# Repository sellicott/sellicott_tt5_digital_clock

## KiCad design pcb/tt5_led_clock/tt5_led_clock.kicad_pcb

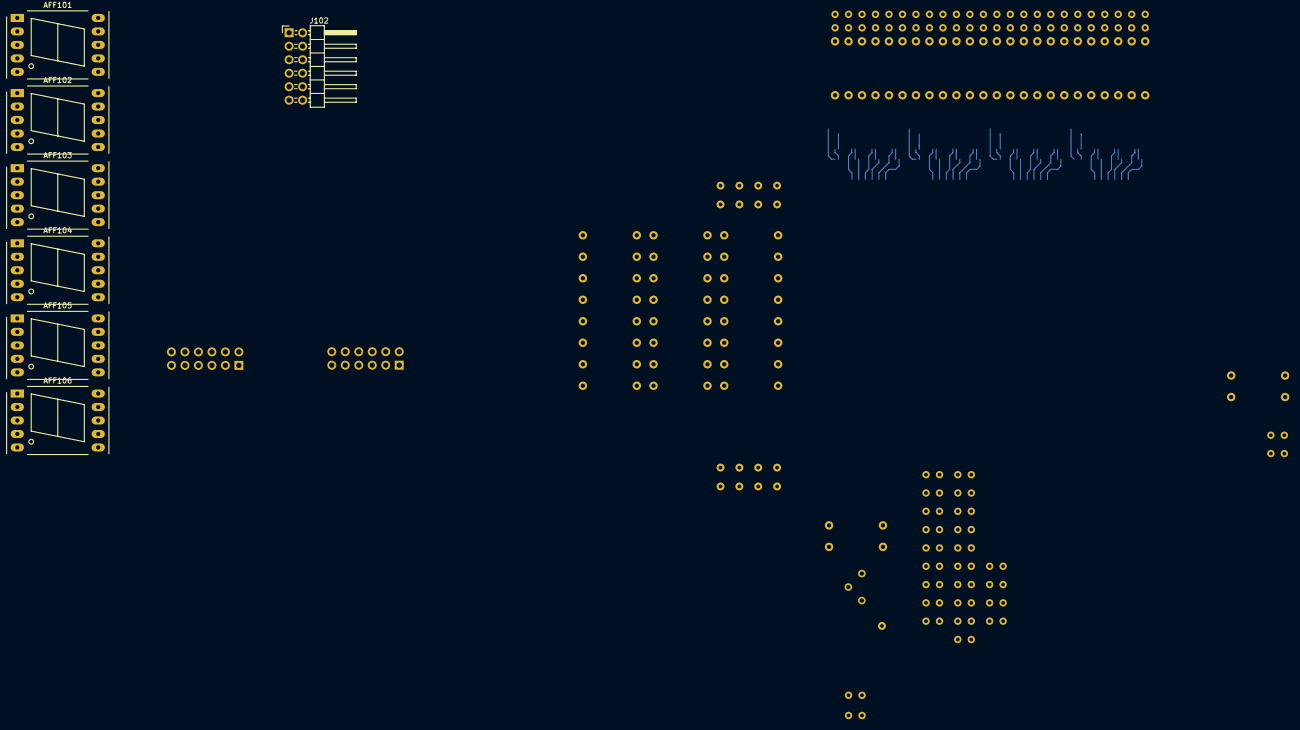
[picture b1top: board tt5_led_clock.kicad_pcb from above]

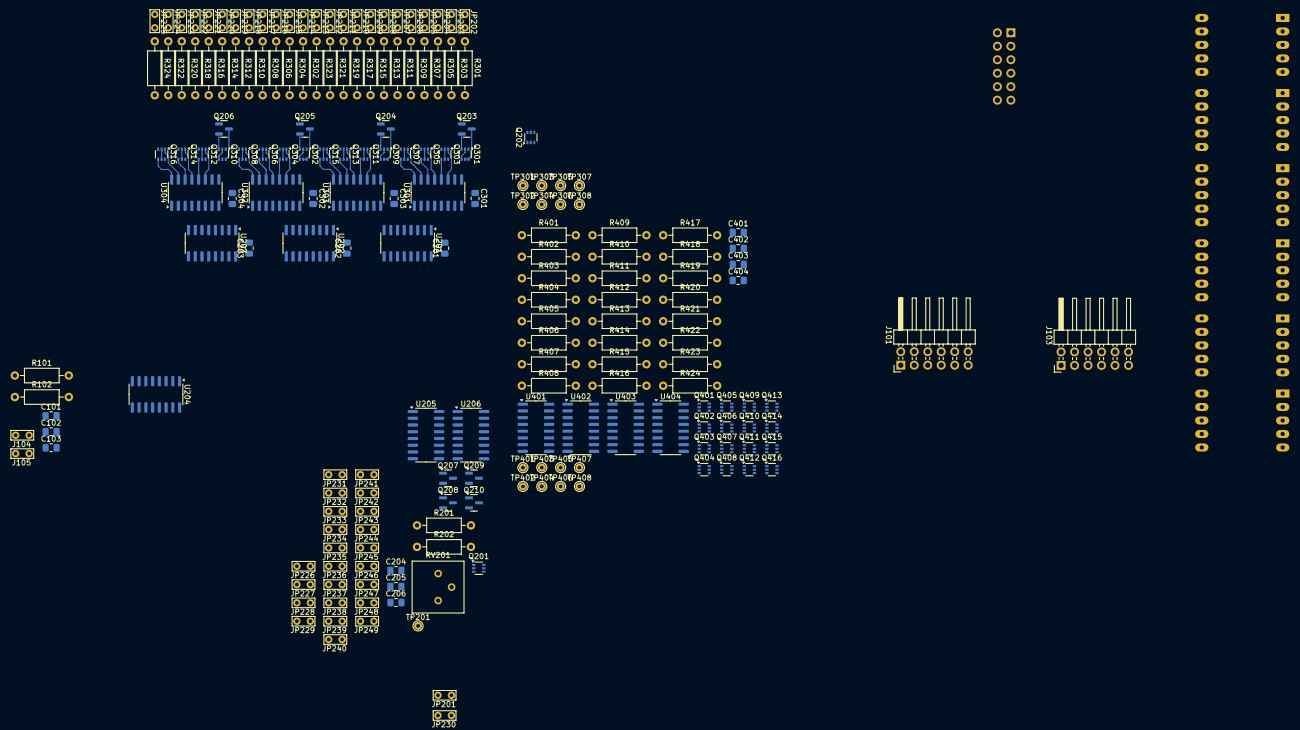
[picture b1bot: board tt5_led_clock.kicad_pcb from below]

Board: 2 copper layers, 203 parts (196 on the bottom side), 188 nets.

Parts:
AFF101, AFF102, AFF103, AFF104, AFF105, AFF106: LTS-6980HR; 7SegmentLED_LTS6760_LTS6780
C101: 10u; C_0805_2012Metric_Pad1.18x1.45mm_HandSolder
C102, C301, C302, C303, C304, C401, C402, C403, C404: 100n; C_0805_2012Metric_Pad1.18x1.45mm_HandSolder
C103: 22u; C_0805_2012Metric_Pad1.18x1.45mm_HandSolder
C201, C202, C203, C204, C205, C206: 1n; C_0805_2012Metric_Pad1.18x1.45mm_HandSolder
J101: Input; PinHeader_2x06_P2.54mm_Horizontal
J102: Bidir; PinHeader_2x06_P2.54mm_Horizontal
J103: Output; PinHeader_2x06_P2.54mm_Horizontal
J104: USB_C_Receptacle_USB2.0_16P; TestPoint_Bridge_Pitch2.54mm_Drill0.7mm
J105: Conn_01x08; TestPoint_Bridge_Pitch2.54mm_Drill0.7mm
JP201, JP202, JP203, JP204, JP205, JP206, JP207, JP208, JP209, JP210, JP211, JP212, JP213, JP214, JP215, JP216, JP217, JP218, JP219, JP220, JP221, JP222, JP223, JP224, JP225, JP226, JP227, JP228, JP229, JP230, JP231, JP232, JP233, JP234, JP235, JP236, JP237, JP238, JP239, JP240, JP241, JP242, JP243, JP244, JP245, JP246, JP247, JP248, JP249: Jumper_2_Bridged; TestPoint_Bridge_Pitch2.54mm_Drill0.7mm
Q201, Q301, Q302, Q303, Q304, Q305, Q306, Q307, Q308, Q309, Q310, Q311, Q312, Q313, Q314, Q315, Q316, Q401, Q402, Q403, Q404, Q405, Q406, Q407, Q408, Q409, Q410, Q411, Q412, Q413, Q414, Q415, Q416: MMDT3904; SOT-363_SC-70-6
Q202: MMDT3906; SOT-363_SC-70-6
Q203, Q204, Q205, Q206, Q207, Q208, Q209, Q210: MMBT3906; SOT-23
R101, R102: 5k1; R_Axial_DIN0207_L6.3mm_D2.5mm_P10.16mm_Horizontal
R201: 10K; R_Axial_DIN0207_L6.3mm_D2.5mm_P10.16mm_Horizontal
R202: 330R; R_Axial_DIN0207_L6.3mm_D2.5mm_P10.16mm_Horizontal
R301, R302, R303, R304, R305, R306, R307, R309, R310, R311, R312, R313, R314, R316, R317, R318, R319, R320, R321, R322, R323, R401, R402, R403, R404, R405, R406, R407, R409, R410, R411, R412, R413, R414, R416, R417, R418, R419, R420, R421, R422, R423: 1k4; R_Axial_DIN0207_L6.3mm_D2.5mm_P10.16mm_Horizontal
R308, R315, R324, R408, R415, R424: 2k8; R_Axial_DIN0207_L6.3mm_D2.5mm_P10.16mm_Horizontal
RV201: 1k; Potentiometer_Bourns_3386P_Vertical
TP201: segment_cm; TestPoint_THTPad_D1.5mm_Drill0.7mm
TP301, TP401: s1_iref; TestPoint_THTPad_D1.5mm_Drill0.7mm
TP302, TP402: s3_iref; TestPoint_THTPad_D1.5mm_Drill0.7mm
TP303, TP403: s1_mirror; TestPoint_THTPad_D1.5mm_Drill0.7mm
TP304, TP404: s3_mirror; TestPoint_THTPad_D1.5mm_Drill0.7mm
TP305, TP405: s2_iref; TestPoint_THTPad_D1.5mm_Drill0.7mm
TP306, TP406: s4_iref; TestPoint_THTPad_D1.5mm_Drill0.7mm
TP307, TP407: s2_mirror; TestPoint_THTPad_D1.5mm_Drill0.7mm
TP308, TP408: s4_mirror; TestPoint_THTPad_D1.5mm_Drill0.7mm
U201, U202, U203, U204, U205, U206: 74HC595; SOIC-16_3.9x9.9mm_P1.27mm
U301, U302, U303, U304, U401, U402, U403, U404: ULN2003; SOIC-16_3.9x9.9mm_P1.27mm

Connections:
+3.3V: C102.1, C103.1
/LED_CC_drivers/LED_Drivers_High/e1_s1a: Q303.1 (E1), R301.2, U301.11 (O6)
/LED_CC_drivers/LED_Drivers_High/e1_s1b: Q303.4 (E2), R303.2, U301.12 (O5)
/LED_CC_drivers/LED_Drivers_High/e1_s1c: Q305.1 (E1), R305.2, U301.13 (O4)
/LED_CC_drivers/LED_Drivers_High/e1_s1d: Q305.4 (E2), R307.2, U301.14 (O3)
/LED_CC_drivers/LED_Drivers_High/e1_s1e: Q307.1 (E1), R309.2, U301.15 (O2)
/LED_CC_drivers/LED_Drivers_High/e1_s1f: Q307.4 (E2), R311.2, U301.16 (O1)
/LED_CC_drivers/LED_Drivers_High/e2_s1dp: Q311.4 (E2), R315.2, U303.12 (O5)
/LED_CC_drivers/LED_Drivers_High/e2_s1g: Q311.1 (E1), R313.2, U303.11 (O6)
/LED_CC_drivers/LED_Drivers_High/e2_s2a: Q313.1 (E1), R317.2, U303.13 (O4)
/LED_CC_drivers/LED_Drivers_High/e2_s2b: Q313.4 (E2), R319.2, U303.14 (O3)
/LED_CC_drivers/LED_Drivers_High/e2_s2c: Q315.1 (E1), R321.2, U303.15 (O2)
/LED_CC_drivers/LED_Drivers_High/e2_s2d: Q315.4 (E2), R323.2, U303.16 (O1)
/LED_CC_drivers/LED_Drivers_High/e3_s2dp: Q306.4 (E2), R308.2, U302.14 (O3)
/LED_CC_drivers/LED_Drivers_High/e3_s2e: Q304.1 (E1), R302.2, U302.11 (O6)
/LED_CC_drivers/LED_Drivers_High/e3_s2f: Q304.4 (E2), R304.2, U302.12 (O5)
/LED_CC_drivers/LED_Drivers_High/e3_s2g: Q306.1 (E1), R306.2, U302.13 (O4)
/LED_CC_drivers/LED_Drivers_High/e3_s3a: Q308.1 (E1), R310.2, U302.15 (O2)
/LED_CC_drivers/LED_Drivers_High/e3_s3b: Q308.4 (E2), R312.2, U302.16 (O1)
/LED_CC_drivers/LED_Drivers_High/e4_s3c: Q312.1 (E1), R314.2, U304.11 (O6)
/LED_CC_drivers/LED_Drivers_High/e4_s3d: Q312.4 (E2), R316.2, U304.12 (O5)
/LED_CC_drivers/LED_Drivers_High/e4_s3dp: Q316.4 (E2), R324.2, U304.16 (O1)
/LED_CC_drivers/LED_Drivers_High/e4_s3e: Q314.1 (E1), R318.2, U304.13 (O4)
/LED_CC_drivers/LED_Drivers_High/e4_s3f: Q314.4 (E2), R320.2, U304.14 (O3)
/LED_CC_drivers/LED_Drivers_High/e4_s3g: Q316.1 (E1), R322.2, U304.15 (O2)
/LED_CC_drivers/LED_Drivers_High/iref1: Q203.3 (C), Q301.5 (B2), Q301.6 (C1), TP301.1
/LED_CC_drivers/LED_Drivers_High/iref2: Q204.3 (C), Q309.5 (B2), Q309.6 (C1), TP305.1
/LED_CC_drivers/LED_Drivers_High/iref3: Q205.3 (C), Q302.5 (B2), Q302.6 (C1), TP302.1
/LED_CC_drivers/LED_Drivers_High/iref4: Q206.3 (C), Q310.5 (B2), Q310.6 (C1), TP306.1
/LED_CC_drivers/LED_Drivers_High/o1_s1a: JP202.1 (A), Q303.6 (C1), R301.1
/LED_CC_drivers/LED_Drivers_High/o1_s1b: JP203.1 (A), Q303.3 (C2), R303.1
/LED_CC_drivers/LED_Drivers_High/o1_s1c: JP204.1 (A), Q305.6 (C1), R305.1
/LED_CC_drivers/LED_Drivers_High/o1_s1d: JP205.1 (A), Q305.3 (C2), R307.1
/LED_CC_drivers/LED_Drivers_High/o1_s1e: JP206.1 (A), Q307.6 (C1), R309.1
/LED_CC_drivers/LED_Drivers_High/o1_s1f: JP207.1 (A), Q307.3 (C2), R311.1
/LED_CC_drivers/LED_Drivers_High/o2_s1dp: JP209.1 (A), Q311.3 (C2), R315.1
/LED_CC_drivers/LED_Drivers_High/o2_s1g: JP208.1 (A), Q311.6 (C1), R313.1
/LED_CC_drivers/LED_Drivers_High/o2_s2a: JP210.1 (A), Q313.6 (C1), R317.1
/LED_CC_drivers/LED_Drivers_High/o2_s2b: JP211.1 (A), Q313.3 (C2), R319.1
/LED_CC_drivers/LED_Drivers_High/o2_s2c: JP212.1 (A), Q315.6 (C1), R321.1
/LED_CC_drivers/LED_Drivers_High/o2_s2d: JP213.1 (A), Q315.3 (C2), R323.1
/LED_CC_drivers/LED_Drivers_High/o3_s2dp: JP217.1 (A), Q306.3 (C2), R308.1
/LED_CC_drivers/LED_Drivers_High/o3_s2e: JP214.1 (A), Q304.6 (C1), R302.1
/LED_CC_drivers/LED_Drivers_High/o3_s2f: JP215.1 (A), Q304.3 (C2), R304.1
/LED_CC_drivers/LED_Drivers_High/o3_s2g: JP216.1 (A), Q306.6 (C1), R306.1
/LED_CC_drivers/LED_Drivers_High/o3_s3a: JP218.1 (A), Q308.6 (C1), R310.1
/LED_CC_drivers/LED_Drivers_High/o3_s3b: JP219.1 (A), Q308.3 (C2), R312.1
/LED_CC_drivers/LED_Drivers_High/o4_s3c: JP220.1 (A), Q312.6 (C1), R314.1
/LED_CC_drivers/LED_Drivers_High/o4_s3d: JP221.1 (A), Q312.3 (C2), R316.1
/LED_CC_drivers/LED_Drivers_High/o4_s3dp: JP225.1 (A), Q316.3 (C2), R324.1
/LED_CC_drivers/LED_Drivers_High/o4_s3e: JP222.1 (A), Q314.6 (C1), R318.1
/LED_CC_drivers/LED_Drivers_High/o4_s3f: JP223.1 (A), Q314.3 (C2), R320.1
/LED_CC_drivers/LED_Drivers_High/o4_s3g: JP224.1 (A), Q316.6 (C1), R322.1
/LED_CC_drivers/LED_Drivers_Low/e1_s1a: Q403.1 (E1), R401.2, U401.11 (O6)
/LED_CC_drivers/LED_Drivers_Low/e1_s1b: Q403.4 (E2), R403.2, U401.12 (O5)
/LED_CC_drivers/LED_Drivers_Low/e1_s1c: Q405.1 (E1), R405.2, U401.13 (O4)
/LED_CC_drivers/LED_Drivers_Low/e1_s1d: Q405.4 (E2), R407.2, U401.14 (O3)
/LED_CC_drivers/LED_Drivers_Low/e1_s1e: Q407.1 (E1), R409.2, U401.15 (O2)
/LED_CC_drivers/LED_Drivers_Low/e1_s1f: Q407.4 (E2), R411.2, U401.16 (O1)
/LED_CC_drivers/LED_Drivers_Low/e2_s1dp: Q411.4 (E2), R415.2, U403.12 (O5)
/LED_CC_drivers/LED_Drivers_Low/e2_s1g: Q411.1 (E1), R413.2, U403.11 (O6)
/LED_CC_drivers/LED_Drivers_Low/e2_s2a: Q413.1 (E1), R417.2, U403.13 (O4)
/LED_CC_drivers/LED_Drivers_Low/e2_s2b: Q413.4 (E2), R419.2, U403.14 (O3)
/LED_CC_drivers/LED_Drivers_Low/e2_s2c: Q415.1 (E1), R421.2, U403.15 (O2)
/LED_CC_drivers/LED_Drivers_Low/e2_s2d: Q415.4 (E2), R423.2, U403.16 (O1)
/LED_CC_drivers/LED_Drivers_Low/e3_s2dp: Q406.4 (E2), R408.2, U402.14 (O3)
/LED_CC_drivers/LED_Drivers_Low/e3_s2e: Q404.1 (E1), R402.2, U402.11 (O6)
/LED_CC_drivers/LED_Drivers_Low/e3_s2f: Q404.4 (E2), R404.2, U402.12 (O5)
/LED_CC_drivers/LED_Drivers_Low/e3_s2g: Q406.1 (E1), R406.2, U402.13 (O4)
/LED_CC_drivers/LED_Drivers_Low/e3_s3a: Q408.1 (E1), R410.2, U402.15 (O2)
/LED_CC_drivers/LED_Drivers_Low/e3_s3b: Q408.4 (E2), R412.2, U402.16 (O1)
/LED_CC_drivers/LED_Drivers_Low/e4_s3c: Q412.1 (E1), R414.2, U404.11 (O6)
/LED_CC_drivers/LED_Drivers_Low/e4_s3d: Q412.4 (E2), R416.2, U404.12 (O5)
/LED_CC_drivers/LED_Drivers_Low/e4_s3dp: Q416.4 (E2), R424.2, U404.16 (O1)
/LED_CC_drivers/LED_Drivers_Low/e4_s3e: Q414.1 (E1), R418.2, U404.13 (O4)
/LED_CC_drivers/LED_Drivers_Low/e4_s3f: Q414.4 (E2), R420.2, U404.14 (O3)
/LED_CC_drivers/LED_Drivers_Low/e4_s3g: Q416.1 (E1), R422.2, U404.15 (O2)
/LED_CC_drivers/LED_Drivers_Low/iref1: Q207.3 (C), Q401.5 (B2), Q401.6 (C1), TP401.1
/LED_CC_drivers/LED_Drivers_Low/iref2: Q208.3 (C), Q409.5 (B2), Q409.6 (C1), TP405.1
/LED_CC_drivers/LED_Drivers_Low/iref3: Q209.3 (C), Q402.5 (B2), Q402.6 (C1), TP402.1
/LED_CC_drivers/LED_Drivers_Low/iref4: Q210.3 (C), Q410.5 (B2), Q410.6 (C1), TP406.1
/LED_CC_drivers/LED_Drivers_Low/o1_s1a: JP226.1 (A), Q403.6 (C1), R401.1
/LED_CC_drivers/LED_Drivers_Low/o1_s1b: JP227.1 (A), Q403.3 (C2), R403.1
/LED_CC_drivers/LED_Drivers_Low/o1_s1c: JP228.1 (A), Q405.6 (C1), R405.1
/LED_CC_drivers/LED_Drivers_Low/o1_s1d: JP229.1 (A), Q405.3 (C2), R407.1
/LED_CC_drivers/LED_Drivers_Low/o1_s1e: JP230.1 (A), Q407.6 (C1), R409.1
/LED_CC_drivers/LED_Drivers_Low/o1_s1f: JP231.1 (A), Q407.3 (C2), R411.1
/LED_CC_drivers/LED_Drivers_Low/o2_s1dp: JP233.1 (A), Q411.3 (C2), R415.1
/LED_CC_drivers/LED_Drivers_Low/o2_s1g: JP232.1 (A), Q411.6 (C1), R413.1
/LED_CC_drivers/LED_Drivers_Low/o2_s2a: JP234.1 (A), Q413.6 (C1), R417.1
/LED_CC_drivers/LED_Drivers_Low/o2_s2b: JP235.1 (A), Q413.3 (C2), R419.1
/LED_CC_drivers/LED_Drivers_Low/o2_s2c: JP236.1 (A), Q415.6 (C1), R421.1
/LED_CC_drivers/LED_Drivers_Low/o2_s2d: JP237.1 (A), Q415.3 (C2), R423.1
/LED_CC_drivers/LED_Drivers_Low/o3_s2dp: JP241.1 (A), Q406.3 (C2), R408.1
/LED_CC_drivers/LED_Drivers_Low/o3_s2e: JP238.1 (A), Q404.6 (C1), R402.1
/LED_CC_drivers/LED_Drivers_Low/o3_s2f: JP239.1 (A), Q404.3 (C2), R404.1
/LED_CC_drivers/LED_Drivers_Low/o3_s2g: JP240.1 (A), Q406.6 (C1), R406.1
/LED_CC_drivers/LED_Drivers_Low/o3_s3a: JP242.1 (A), Q408.6 (C1), R410.1
/LED_CC_drivers/LED_Drivers_Low/o3_s3b: JP243.1 (A), Q408.3 (C2), R412.1
/LED_CC_drivers/LED_Drivers_Low/o4_s3c: JP244.1 (A), Q412.6 (C1), R414.1
/LED_CC_drivers/LED_Drivers_Low/o4_s3d: JP245.1 (A), Q412.3 (C2), R416.1
/LED_CC_drivers/LED_Drivers_Low/o4_s3dp: JP249.1 (A), Q416.3 (C2), R424.1
/LED_CC_drivers/LED_Drivers_Low/o4_s3e: JP246.1 (A), Q414.6 (C1), R418.1
/LED_CC_drivers/LED_Drivers_Low/o4_s3f: JP247.1 (A), Q414.3 (C2), R420.1
/LED_CC_drivers/LED_Drivers_Low/o4_s3g: JP248.1 (A), Q416.6 (C1), R422.1
/LED_CC_drivers/h1_a: U201.1 (QB), U301.6 (I6)
/LED_CC_drivers/h1_b: U201.2 (QC), U301.5 (I5)
/LED_CC_drivers/h1_c: U201.3 (QD), U301.4 (I4)
/LED_CC_drivers/h1_d: U201.4 (QE), U301.3 (I3)
/LED_CC_drivers/h1_e: U201.5 (QF), U301.2 (I2)
/LED_CC_drivers/h1_f: U201.6 (QG), U301.1 (I1)
/LED_CC_drivers/h1_g: U201.7 (QH), U303.6 (I6)
/LED_CC_drivers/h1_p: U201.15 (QA), U303.5 (I5)
/LED_CC_drivers/h2_a: U202.1 (QB), U303.4 (I4)
/LED_CC_drivers/h2_b: U202.2 (QC), U303.3 (I3)
/LED_CC_drivers/h2_c: U202.3 (QD), U303.2 (I2)
/LED_CC_drivers/h2_d: U202.4 (QE), U303.1 (I1)
/LED_CC_drivers/h2_e: U202.5 (QF), U302.6 (I6)
/LED_CC_drivers/h2_f: U202.6 (QG), U302.5 (I5)
/LED_CC_drivers/h2_g: U202.7 (QH), U302.4 (I4)
/LED_CC_drivers/h2_p: U202.15 (QA), U302.3 (I3)
/LED_CC_drivers/m1_a: U203.1 (QB), U302.2 (I2)
/LED_CC_drivers/m1_b: U203.2 (QC), U302.1 (I1)
/LED_CC_drivers/m1_c: U203.3 (QD), U304.6 (I6)
/LED_CC_drivers/m1_d: U203.4 (QE), U304.5 (I5)
/LED_CC_drivers/m1_e: U203.5 (QF), U304.4 (I4)
/LED_CC_drivers/m1_f: U203.6 (QG), U304.3 (I3)
/LED_CC_drivers/m1_g: U203.7 (QH), U304.2 (I2)
/LED_CC_drivers/m1_p: U203.15 (QA), U304.1 (I1)
/LED_CC_drivers/m2_a: U204.1 (QB), U401.6 (I6)
/LED_CC_drivers/m2_b: U204.2 (QC), U401.5 (I5)
/LED_CC_drivers/m2_c: U204.3 (QD), U401.4 (I4)
/LED_CC_drivers/m2_d: U204.4 (QE), U401.3 (I3)
/LED_CC_drivers/m2_e: U204.5 (QF), U401.2 (I2)
/LED_CC_drivers/m2_f: U204.6 (QG), U401.1 (I1)
/LED_CC_drivers/m2_g: U204.7 (QH), U403.6 (I6)
/LED_CC_drivers/m2_p: U204.15 (QA), U403.5 (I5)
/LED_CC_drivers/oe: U201.13 (~OE), U202.13 (~OE), U203.13 (~OE), U204.13 (~OE), U205.13 (~OE), U206.13 (~OE)
/LED_CC_drivers/s1_a: U205.1 (QB), U403.4 (I4)
/LED_CC_drivers/s1_b: U205.2 (QC), U403.3 (I3)
/LED_CC_drivers/s1_c: U205.3 (QD), U403.2 (I2)
/LED_CC_drivers/s1_d: U205.4 (QE), U403.1 (I1)
/LED_CC_drivers/s1_e: U205.5 (QF), U402.6 (I6)
/LED_CC_drivers/s1_f: U205.6 (QG), U402.5 (I5)
/LED_CC_drivers/s1_g: U205.7 (QH), U402.4 (I4)
/LED_CC_drivers/s1_p: U205.15 (QA), U402.3 (I3)
/LED_CC_drivers/s2_a: U206.1 (QB), U402.2 (I2)
/LED_CC_drivers/s2_b: U206.2 (QC), U402.1 (I1)
/LED_CC_drivers/s2_c: U206.3 (QD), U404.6 (I6)
/LED_CC_drivers/s2_d: U206.4 (QE), U404.5 (I5)
/LED_CC_drivers/s2_e: U206.5 (QF), U404.4 (I4)
/LED_CC_drivers/s2_f: U206.6 (QG), U404.3 (I3)
/LED_CC_drivers/s2_g: U206.7 (QH), U404.2 (I2)
/LED_CC_drivers/s2_p: U206.15 (QA), U404.1 (I1)
/LED_CC_drivers/sc_clr: U201.10 (~SRCLR), U202.10 (~SRCLR), U203.10 (~SRCLR), U204.10 (~SRCLR), U205.10 (~SRCLR), U206.10 (~SRCLR)
/sc_clk: J103.3, U201.11 (SRCLK), U202.11 (SRCLK), U203.11 (SRCLK), U204.11 (SRCLK), U205.11 (SRCLK), U206.11 (SRCLK)
/sc_latch: J103.2, U201.12 (RCLK), U202.12 (RCLK), U203.12 (RCLK), U204.12 (RCLK), U205.12 (RCLK), U206.12 (RCLK)
/sc_mosi: J103.1, U201.14 (SER)
GND: C101.2, C102.2, C103.2, C201.2, C202.2, C203.2, C204.2, C205.2, C206.2, C301.2, C302.2, C303.2, C304.2, C401.2, C402.2, C403.2, C404.2, J101.5, J101.11, J102.5, J102.11, J103.5, J103.11, Q201.1 (E1), Q202.3 (C2), R101.2, R102.2, RV201.3, U201.8 (GND), U202.8 (GND), U203.8 (GND), U204.8 (GND), U205.8 (GND), U206.8 (GND), U301.8 (GND), U302.8 (GND), U303.8 (GND), U304.8 (GND), U401.8 (GND), U402.8 (GND), U403.8 (GND), U404.8 (GND)
unnamed: J101.6, J101.12, J102.6, J102.12, J103.6, J103.12
unnamed: JP201.1 (A), Q201.3 (C2)
unnamed: Q202.5 (B2), Q202.6 (C1)
unnamed: Q201.2 (B1), Q201.4 (E2), R202.1
unnamed: Q201.5 (B2), Q201.6 (C1), R201.2
unnamed: Q202.2 (B1), Q202.4 (E2), Q203.1 (B), Q204.1 (B), Q205.1 (B), Q206.1 (B), Q207.1 (B), Q208.1 (B), Q209.1 (B), Q210.1 (B), TP201.1
unnamed: Q301.2 (B1), Q301.4 (E2), Q303.2 (B1), Q303.5 (B2), Q305.2 (B1), Q305.5 (B2), Q307.2 (B1), Q307.5 (B2), TP303.1
unnamed: Q301.1 (E1), U301.10 (O7)
unnamed: Q302.2 (B1), Q302.4 (E2), Q304.2 (B1), Q304.5 (B2), Q306.2 (B1), Q306.5 (B2), Q308.2 (B1), Q308.5 (B2), TP304.1
unnamed: Q302.1 (E1), U302.10 (O7)
unnamed: Q309.2 (B1), Q309.4 (E2), Q311.2 (B1), Q311.5 (B2), Q313.2 (B1), Q313.5 (B2), Q315.2 (B1), Q315.5 (B2), TP307.1
unnamed: Q309.1 (E1), U303.10 (O7)
unnamed: Q310.2 (B1), Q310.4 (E2), Q312.2 (B1), Q312.5 (B2), Q314.2 (B1), Q314.5 (B2), Q316.2 (B1), Q316.5 (B2), TP308.1
unnamed: Q310.1 (E1), U304.10 (O7)
unnamed: Q401.2 (B1), Q401.4 (E2), Q403.2 (B1), Q403.5 (B2), Q405.2 (B1), Q405.5 (B2), Q407.2 (B1), Q407.5 (B2), TP403.1
unnamed: Q401.1 (E1), U401.10 (O7)
unnamed: Q402.2 (B1), Q402.4 (E2), Q404.2 (B1), Q404.5 (B2), Q406.2 (B1), Q406.5 (B2), Q408.2 (B1), Q408.5 (B2), TP404.1
unnamed: Q402.1 (E1), U402.10 (O7)
unnamed: Q409.2 (B1), Q409.4 (E2), Q411.2 (B1), Q411.5 (B2), Q413.2 (B1), Q413.5 (B2), Q415.2 (B1), Q415.5 (B2), TP407.1
unnamed: Q409.1 (E1), U403.10 (O7)
unnamed: Q410.2 (B1), Q410.4 (E2), Q412.2 (B1), Q412.5 (B2), Q414.2 (B1), Q414.5 (B2), Q416.2 (B1), Q416.5 (B2), TP408.1
unnamed: Q410.1 (E1), U404.10 (O7)
unnamed: R202.2, RV201.1, RV201.2
unnamed: U201.9 (QH'), U202.14 (SER)
unnamed: U202.9 (QH'), U203.14 (SER)
unnamed: U203.9 (QH'), U204.14 (SER)
unnamed: U204.9 (QH'), U205.14 (SER)
unnamed: U205.9 (QH'), U206.14 (SER)
VDD: AFF101.3 (C.K.), AFF101.8 (C.K.), AFF102.3 (C.K.), AFF102.8 (C.K.), AFF103.3 (C.K.), AFF103.8 (C.K.), AFF104.3 (C.K.), AFF104.8 (C.K.), AFF105.3 (C.K.), AFF105.8 (C.K.), AFF106.3 (C.K.), AFF106.8 (C.K.), C201.1, C202.1, C203.1, C204.1, C205.1, C206.1, C301.1, C302.1, C303.1, C304.1, C401.1, C402.1, C403.1, C404.1, Q202.1 (E1), Q203.2 (E), Q204.2 (E), Q205.2 (E), Q206.2 (E), Q207.2 (E), Q208.2 (E), Q209.2 (E), Q210.2 (E), Q301.3 (C2), Q302.3 (C2), Q309.3 (C2), Q310.3 (C2), Q401.3 (C2), Q402.3 (C2), Q409.3 (C2), Q410.3 (C2), R201.1, U201.16 (VCC), U202.16 (VCC), U203.16 (VCC), U204.16 (VCC), U205.16 (VCC), U206.16 (VCC), U301.7 (I7), U301.9 (COM), U302.7 (I7), U302.9 (COM), U303.7 (I7), U303.9 (COM), U304.7 (I7), U304.9 (COM), U401.7 (I7), U401.9 (COM), U402.7 (I7), U402.9 (COM), U403.7 (I7), U403.9 (COM), U404.7 (I7), U404.9 (COM)

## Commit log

2023-11-04 moved files from old repo
2023-11-04 updated yaml formatting
2023-11-04 fix misnamed verilog filename
2023-11-04 fix stray number in code
2023-11-04 added timescale, fixed output ports not connected
2023-11-04 updated documentation
2023-11-04 added widths to constants
2023-11-04 removed the timeset clock from the reference clock generator
2023-11-04 reduced the size of the debounce counter register
2023-11-04 reduced sizes a little more
2023-11-04 Reduced the size of the timeset registers.
2023-11-04 remove some debouncing on switches
2023-11-04 updated to 1x2 tile
2023-11-04 update debounce count
2024-10-29 Add initial PCB design schematics/pcb
2024-10-29 added PDF of PCB schematic
